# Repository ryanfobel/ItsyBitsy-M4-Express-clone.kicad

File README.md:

# ItsyBitsy-M4-Express-PCB-clone
KiCad version of Adafruit's [ItsyBitsy M4 Express PCB](https://github.com/adafruit/Adafruit-ItsyBitsy-M4-Express-PCB)
design files. Conversion from Eagle was performed using [these eagle-to-kicad scripts](https://github.com/lachlanA/eagle-to-kicad).

For more details on Adafruit's ItsyBitsy M4 Express, check out the product pages at

   * https://www.adafruit.com/products/3800

Adafruit invests time and resources providing this open source design, 
please support Adafruit and open-source hardware by purchasing 
products from Adafruit!

Designed by Adafruit Industries.  
Creative Commons Attribution, Share-Alike license, check license.txt for more information.  
All text above must be included in any redistribution.  
Conversion from Eagle to KiCad by Ryan Fobel.

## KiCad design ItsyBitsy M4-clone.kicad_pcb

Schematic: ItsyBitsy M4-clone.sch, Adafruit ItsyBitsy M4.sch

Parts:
C1: 1uF; MICROBUILDER__0603MP; MPN CL10B105KP8NNNC
C5, C7, C14: 1uF; MICROBUILDER_0603-NO; MPN CL10B105KP8NNNC
C6, C8: 10~F; MICROBUILDER_0805-NO; MPN C0805C106K8PACTU
C9: 10uF; MICROBUILDER__0805MP; MPN C0805C106K8PACTU
D1, D2: MBR120; ADAFRUIT_SOD-123FL; MPN MBR120VLSFT3G
IC1: 74HCT1G125DBV; 74XX-LITTLE-US_SOT23-5; MPN SN74AHCT1G125DBVR
IC2: ATSAMD51G_TQFN48; MICROBUILDER_TQFN48_7MM; MPN ATSAMD51G19A-MU
JP1: MICROBUILDER_1X05_ROUND_70
JP2, JP4: MICROBUILDER_1X14_ROUND70
L2: AP102-2020; MICROBUILDER_APA102_2020; MPN APA102-2020
L36: RED; MICROBUILDER_CHIPLED_0603_NOOUTLINE; MPN 150060RS75000
R1, R2: 100k; MICROBUILDER_0603-NO; MPN ESR03EZPJ104
R3: 2.2K; MICROBUILDER__0603MP; MPN ERJ-3GEYJ222V
R4: 10K; MICROBUILDER__0603MP; MPN ERJ-3GEYJ103V
R7: 2.2K; MICROBUILDER_0603-NO; MPN ERJ-3GEYJ222V
SJ1: MICROBUILDER_SOLDERJUMPER_CLOSEDWIRE
SW1: SPST_TACT-KMR2; ADAFRUIT_KMR2; MPN KMR231NG LFS
U1: GD25x16; MICROBUILDER_USON8; MPN GD25Q16CTIGR
U2: AP2112K-3.3; MICROBUILDER_SOT23-5; MPN AP2112K-3.3TRG1
X3: microUSB; MICROBUILDER_4UCONN_20329_V2; MPN 10118194-0001LF

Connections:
+3V3: C5.1, C7.1, C8.1, IC2.6 (VDDA), IC2.17 (VDDIO), IC2.36 (VDDIO), IC2.44 (VDDIO), JP4.13, L2.3 (VDD), R2.1, R3.2, R4.1, SJ1.2, U1.8 (VCC), U2.5 (OUT)
/A0: IC2.3 (PA02/EINT2/AIN0/VOUT0), JP4.10
/A1: IC2.10 (PA05/I5/AIN5/VOUT1/SERCOM0.1), JP4.9
/A2: IC2.7 (PB08/I8/AIN2/SERCOM4.0), JP4.8
/A3: IC2.8 (PB09/I9/AIN3/SERCOM4.1), JP4.7
/A4: IC2.9 (PA04/I4/VREFB/AIN4/SERCOM0.0), JP4.6
/A5: IC2.11 (PA06/I6/VREFC/AIN6/SERCOM0.2), JP4.5
/AREF: C14.1, IC2.4 (PA03/I3/VREFA/AIN1), JP4.12, SJ1.1
/D2: IC2.12 (PA07/I7/AIN7/SERCOM0.3), JP4.1
/D3: IC2.37 (PB22/I6/SERCOM1+5.2), JP1.4
/D4: IC2.23 (PA14/I14/SERCOM2+4.2), JP1.5
/D5: IC1.2 (I), IC2.24 (PA15/I15/SERCOM2+4.3)
/D5_5V: IC1.4 (O), JP2.10
/D7: IC2.27 (PA18/I2/SERCOM1+3.2), JP2.9
/D9: IC2.28 (PA19/I3/SERCOM1+3.3), JP2.8
/D10: IC2.29 (PA20/I4/SERCOM3+5.2/I2SFS0), JP2.7
/D11: IC2.30 (PA21/I5/SERCOM3+5.3/I2SDO), JP2.6
/D12: IC2.32 (PA23/I2C/I7/SERCOM3.1+5.0/SOF/I2SFS1), JP2.5
/D13: IC2.31 (PA22/I2C/I6/SERCOM3.0+5.1/I2SDI), JP2.4, R7.1
/D+: IC2.34 (PA25/I9/SERCOM3+5.3/D+), X3.D+
/D-: IC2.33 (PA24/I8/SERCOM3+5.2/D-), X3.D-
/DOTSTAR_CLK: IC2.47 (PB02/I2/AIN14/SERCOM5.0), L2.5 (CKI)
/DOTSTAR_DATA: IC2.48 (PB03/I3/AIN15/SERCOM5.1), L2.6 (DI)
/EN: JP1.1, R1.2, U2.3 (EN)
/MISO: IC2.38 (PB23/I7/SERCOM1+5.3), JP4.2
/MOSI: IC2.1 (PA00/EINT0/SERCOM1.0), JP4.3
/N$2: L36.A, R7.2
/QSPI_CS: IC2.20 (PB11/I11/SERCOM4.3/I2SFS1), R2.2, U1.1 (SSEL)
/QSPI_DATA[0]: IC2.13 (PA08/I2C/AIN8/SERCOM0.0+2.1/I2SMCK), U1.5 (MOSI)
/QSPI_DATA[1]: IC2.14 (PA09/I2C/I9/AIN9/SERCOM0.1+2.0/I2SFS0), U1.2 (MISO)
/QSPI_DATA[2]: IC2.15 (PA10/I10/AIN10/SERCOM0+2.2/I2SCK), U1.3 (WP#/IO2)
/QSPI_DATA[3]: IC2.16 (PA11/I11/AIN11/SERCOM0+2.3/I2SDO), U1.7 (HOLD#/IO3)
/QSPI_SCK: IC2.19 (PB10/I10/SERCOM4.2/I2SDI), U1.6 (SCK)
/RX_D0: IC2.25 (PA16/I2C/I0/SERCOM1.0+3.1), JP2.14
/SCK: IC2.2 (PA01/EINT1/SERCOM1.1), JP4.4
/SCL: IC2.22 (PA13/I13/I2C/SERCOM2.1+4.0), JP2.11
/SDA: IC2.21 (PA12/I12/I2C/SERCOM2.0+4.1), JP2.12
/SWCLK: IC2.45 (PA30/I14/SECOM1.2/SWCLK), JP1.3, R3.1
/SWDIO: IC2.46 (PA31/I15/SECOM1.3/SWDIO), JP1.2
/TX_D1: IC2.26 (PA17/I2C/I1/SERCOM1.1+3.0), JP2.13
/VDDCORE: C9.1, IC2.41 (VDDCORE)
/VHI: C6.1, D1.C, D2.C, IC1.5 (VCC), JP4.11, R1.1, U2.1 (IN)
/~RESET: C1.2, IC2.40 (/RESET), JP4.14, R4.2, SW1.1, SW1.3 (P1)
GND: C1.1, C5.2, C6.2, C7.2, C8.2, C9.2, C14.2, IC1.1 (OE), IC1.3 (GND), IC2.5 (GNDA), IC2.18 (GND), IC2.35 (GND), IC2.42 (GND), IC2.THER (TP), JP2.2, L2.4 (GND), L36.C, SW1.2 (S), SW1.4 (S1), U1.4 (VSS), U2.2 (GND), X3.BASE (GND), X3.GND, X3.SPRT (GND); also elsewhere on the board
VBAT: D1.A, JP2.1
VBUS: D2.A, JP2.3, X3.VBUS

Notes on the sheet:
POWER AND FILTERING
RESET
SERCOM0: (avail on A1, A4, A5, D2) SERCOM1: SPI SERCOM2: I2C SERCOM3: UART SERCOM4: (NEOPIX DMA MOSI) SERCOM5: (avail on D10-D13)
PCCDEN1
PCCDEN2
PCCD0
PCCD1
PCCD2
PCCD3
PCCD4
PCCD5
PCCD6
PCCD7
PCCLK

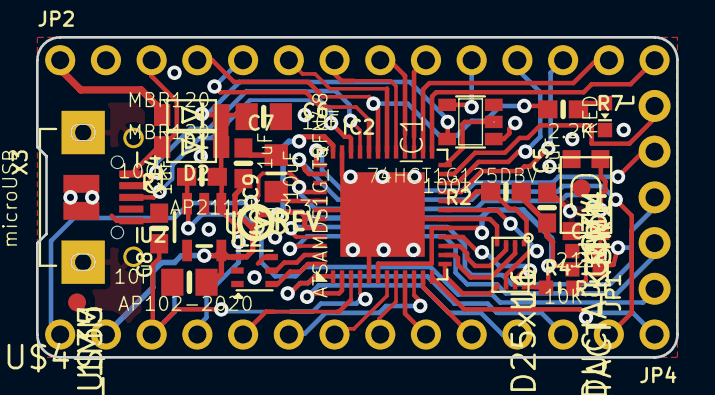
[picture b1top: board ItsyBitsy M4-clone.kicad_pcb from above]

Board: 4 copper layers, 35.6 x 17.8 mm, 31 parts (0 on the bottom side), 45 nets.

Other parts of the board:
L: RED; CHIPLED_0603_NOOUTLINE
U$4: ITSYM4_TOP
U$5: ITSYM4_BOT
U$6: PCBFEAT-REV-040
U$34, U$35: FIDUCIAL_1MM

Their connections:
GND: L.C; also elsewhere on the board

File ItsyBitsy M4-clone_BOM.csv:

Reference,Value,Footprint,Datasheet,MPN
C1,1uF,MICROBUILDER__0603MP,,CL10B105KP8NNNC
"C5, C7, C14",1uF,MICROBUILDER_0603-NO,,CL10B105KP8NNNC
"C6, C8",10uF,MICROBUILDER_0805-NO,,C0805C106K8PACTU
C9,10uF,MICROBUILDER__0805MP,,C0805C106K8PACTU
"D1, D2",MBR120,ADAFRUIT_SOD-123FL,,MBR120VLSFT3G
IC1,74HCT1G125DBV,74XX-LITTLE-US_SOT23-5,,SN74AHCT1G125DBVR
IC2,ATSAMD51G_TQFN48,MICROBUILDER_TQFN48_7MM,,ATSAMD51G19A-MU
JP1,~,MICROBUILDER_1X05_ROUND_70,,
"JP2, JP4",~,MICROBUILDER_1X14_ROUND70,,
L2,AP102-2020,MICROBUILDER_APA102_2020,,APA102-2020
L36,RED,MICROBUILDER_CHIPLED_0603_NOOUTLINE,,150060RS75000
"R1, R2",100k,MICROBUILDER_0603-NO,,ESR03EZPJ104
R3,2.2K,MICROBUILDER__0603MP,,ERJ-3GEYJ222V
R4,10K,MICROBUILDER__0603MP,,ERJ-3GEYJ103V
R7,2.2K,MICROBUILDER_0603-NO,,ERJ-3GEYJ222V
SJ1,~,MICROBUILDER_SOLDERJUMPER_CLOSEDWIRE,,
SW1,SPST_TACT-KMR2,ADAFRUIT_KMR2,,KMR231NG LFS
U1,GD25x16,MICROBUILDER_USON8,,GD25Q16CTIGR
U2,AP2112K-3.3,MICROBUILDER_SOT23-5,,AP2112K-3.3TRG1
X3,microUSB,MICROBUILDER_4UCONN_20329_V2,,10118194-0001LF
